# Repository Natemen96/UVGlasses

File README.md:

# UVGlasses

In 2014 **76,665** people in the United States were diagnosed with skin cancer

In 2014 **9,324** people in the United States died from skin cancer

The CDC recommends that the best method of prevention of melanoma is avoiding the sun, and as little as 15 minutes of exposure to the sun can be enough to damage the skin

The UV Glasses is our solution this issue, it's a wearable device that provide a convenient and innovative means of monitoring harmful UV ray exposure while presenting data real-time via mobile device.

**FUTURE DEVELOPMENTS**

•Reduce product size

•Mobile device notification alerts

•Enable users to save data for further analysis

•Expand app functionality to iOS platforms

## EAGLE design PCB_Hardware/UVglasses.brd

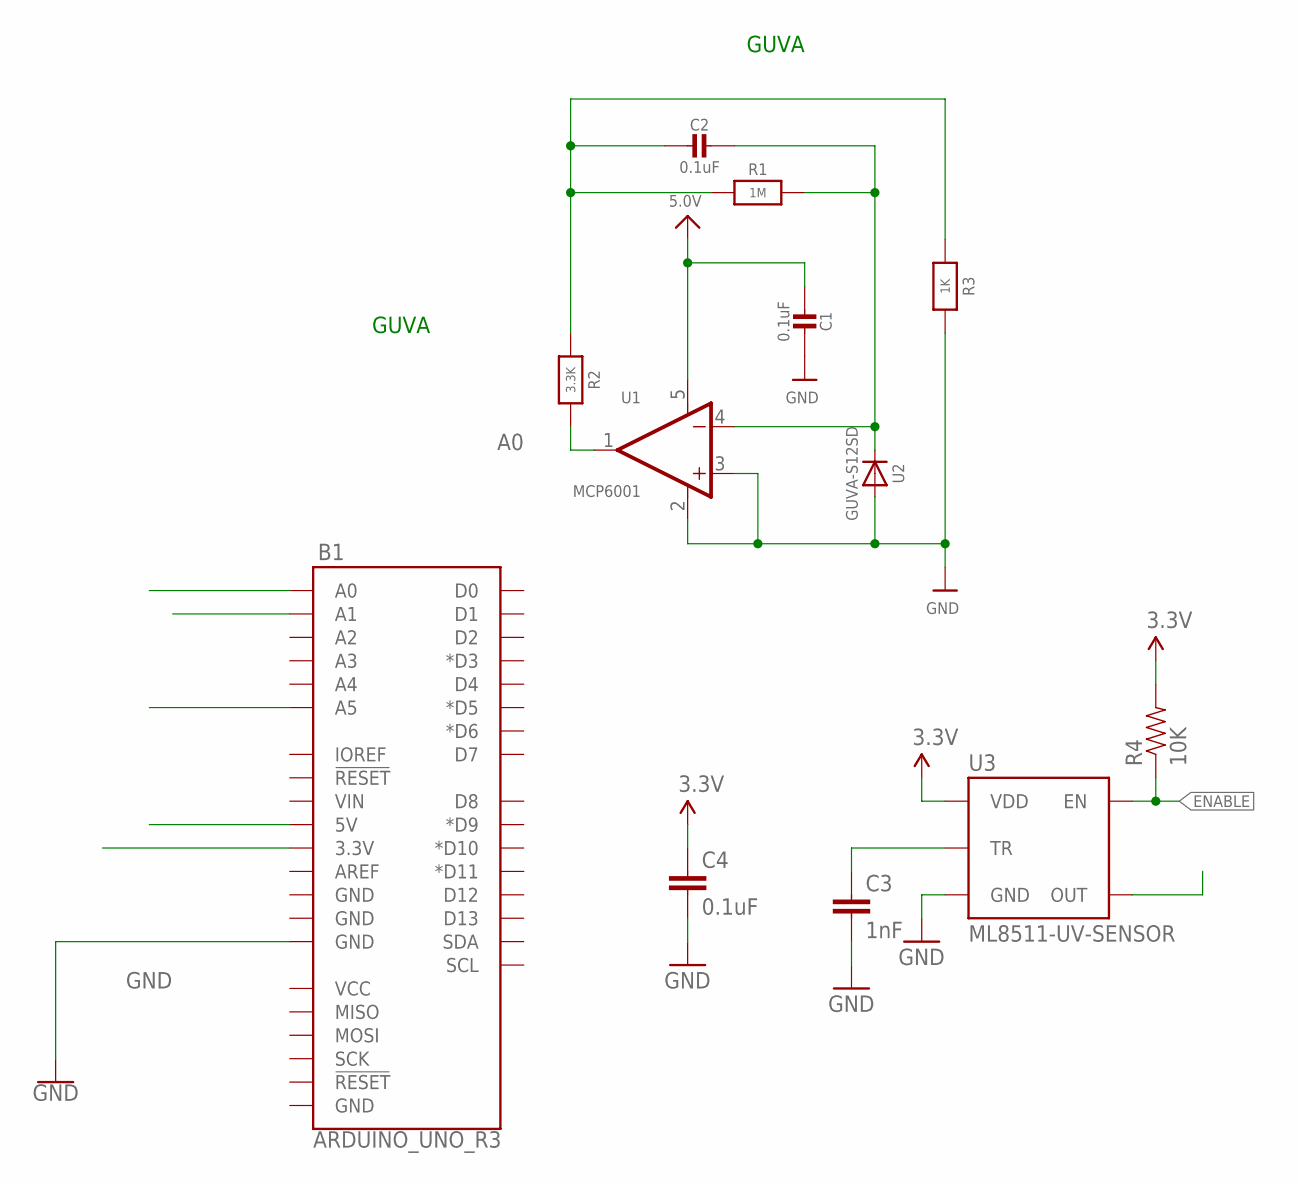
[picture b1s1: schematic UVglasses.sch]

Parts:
B1: ARDUINO_UNO_R3; ARDUINO_R3
C1, C2: 0.1uF; 0805-NO
C3: 1nF; 0603-CAP
C4: 0.1uF; 0603-CAP
R1: 1M; 0805-NO
R2: 3.3K; 0805-NO
R3: 1K; 0805-NO
R4: 10K; 0603-RES
U1: MCP6001; SOT23-5
U2: GUVA-S12SD
U3: ML8511-UV-SENSOR; ML8511

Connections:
3.3V: B1.3.3V, B1.A5, C4.1, R4.2, U3.7 (VDD)
5.0V: B1.5V, C1.1, U1.5 (V+)
A0: B1.A0, R2.1, U1.1 (OUT)
A1: B1.A1, U3.8 (OUT)
ENABLE: R4.1, U3.4 (EN)
GND: B1.GND@2 (GND), C1.2, C3.2, C4.2, R3.1, U1.2 (V-), U1.3 (+IN), U2.A, U3.5 (GND)
unnamed: C2.1, R1.2, R2.2, R3.2
unnamed: C2.2, R1.1, U1.4 (-IN), U2.K (C)
unnamed: C3.1, U3.10 (TR)

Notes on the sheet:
GUVA

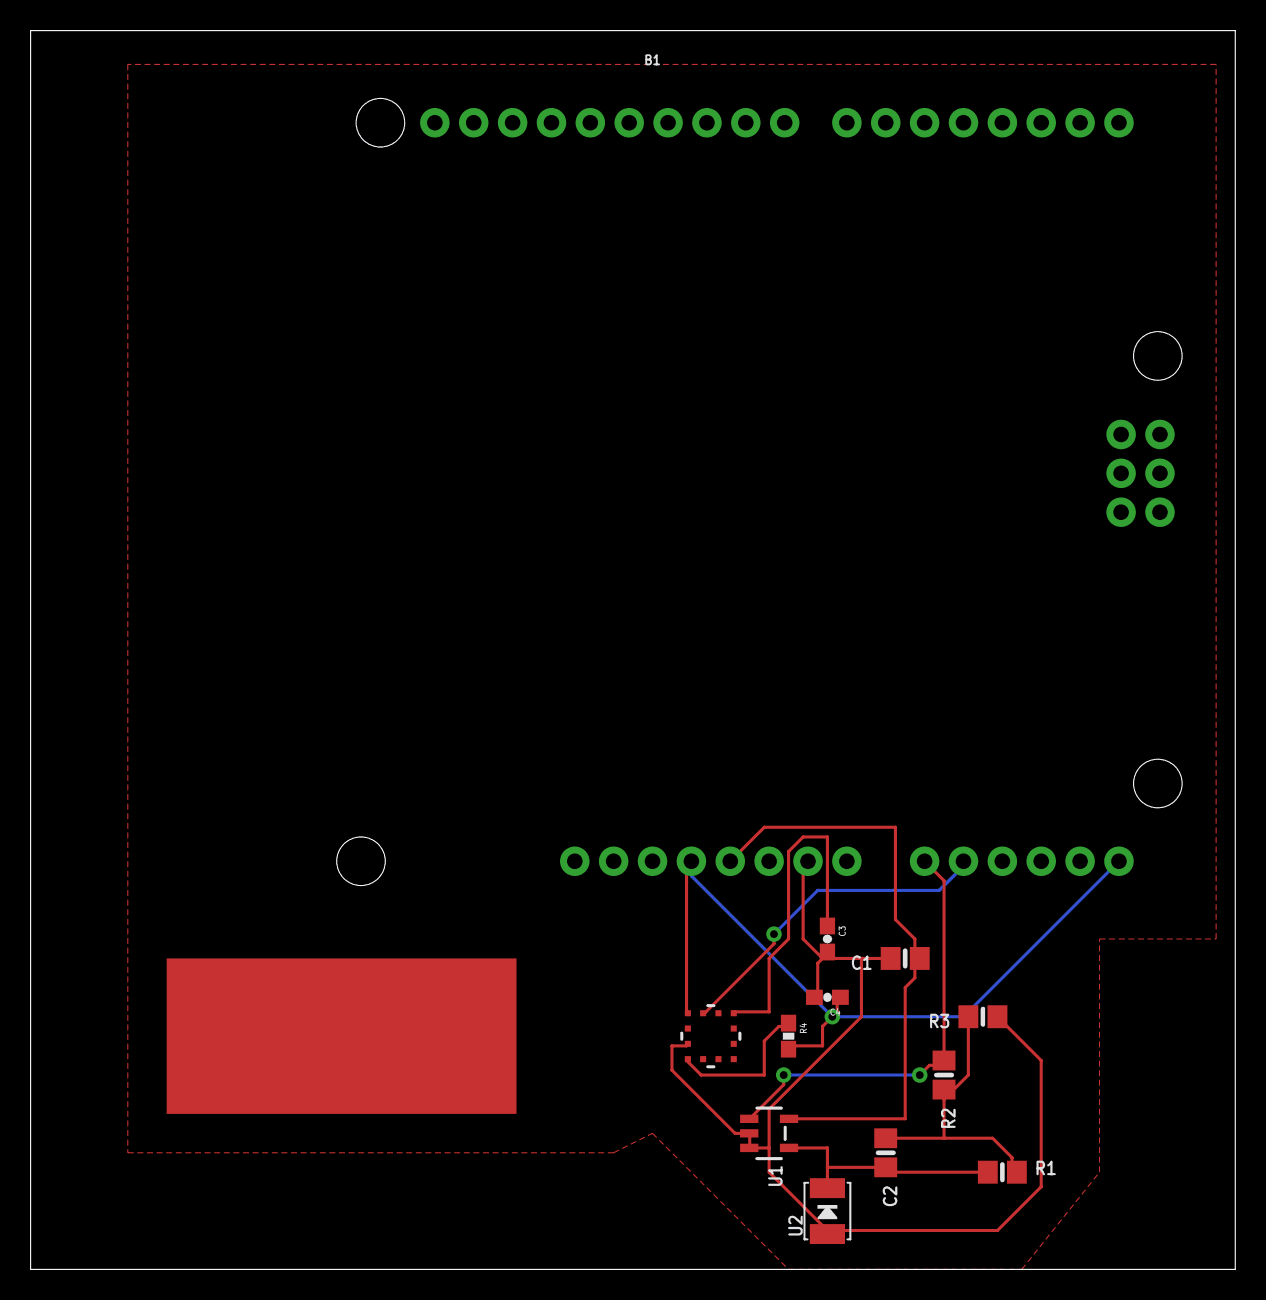
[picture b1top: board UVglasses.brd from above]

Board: 2 copper layers, 78.7 x 81.0 mm, 12 parts (0 on the bottom side), 9 nets.

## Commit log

2018-02-25 Cleaned up Repository
2018-02-25 small changes
2019-05-19 Issue with Github cloning

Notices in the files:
parts and their libraries:
SparkFun-Boards: Licensing: Creative Commons ShareAlike 4.0 International - https://creativecommons.org/licenses/by-sa/4.0
microbuilder: This work is placed in the public domain, and may be freely used for commercial and non-commercial work with the following conditions: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
